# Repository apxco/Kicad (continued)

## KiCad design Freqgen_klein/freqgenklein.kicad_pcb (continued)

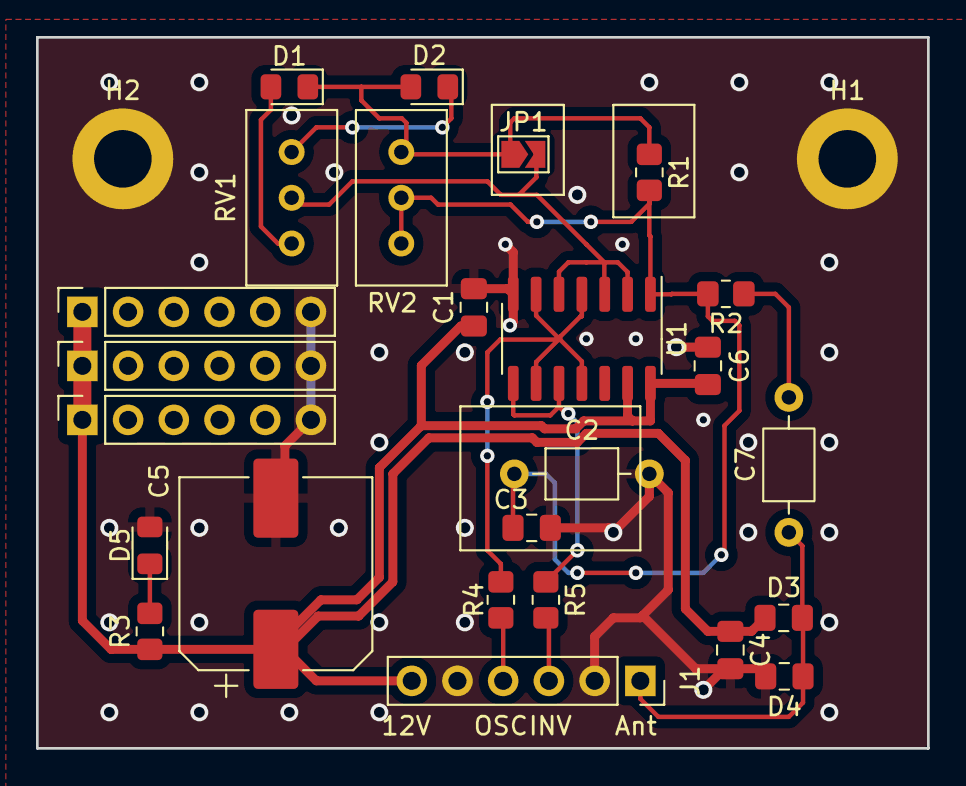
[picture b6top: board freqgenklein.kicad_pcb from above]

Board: 2 copper layers, 49.5 x 39.5 mm, 27 parts (0 on the bottom side), 14 nets.

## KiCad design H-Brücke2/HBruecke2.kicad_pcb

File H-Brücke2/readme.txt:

Aufbau einer H-Brücke mit eigenem Oszillator.

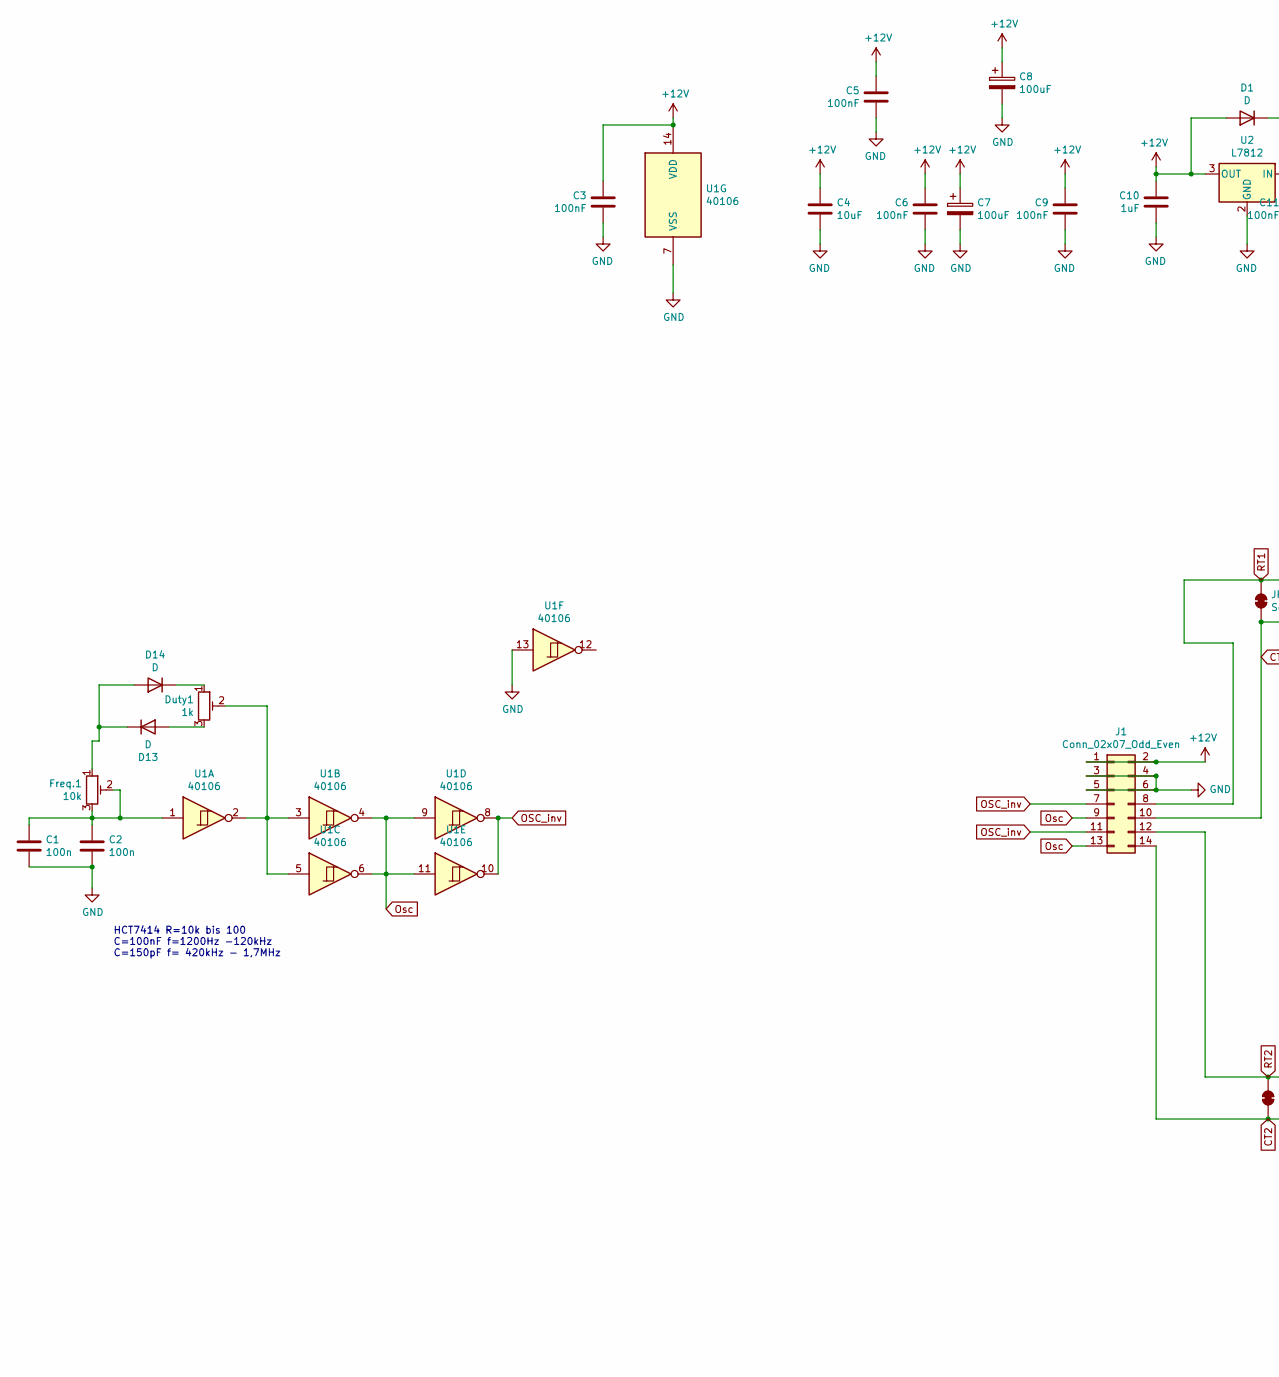
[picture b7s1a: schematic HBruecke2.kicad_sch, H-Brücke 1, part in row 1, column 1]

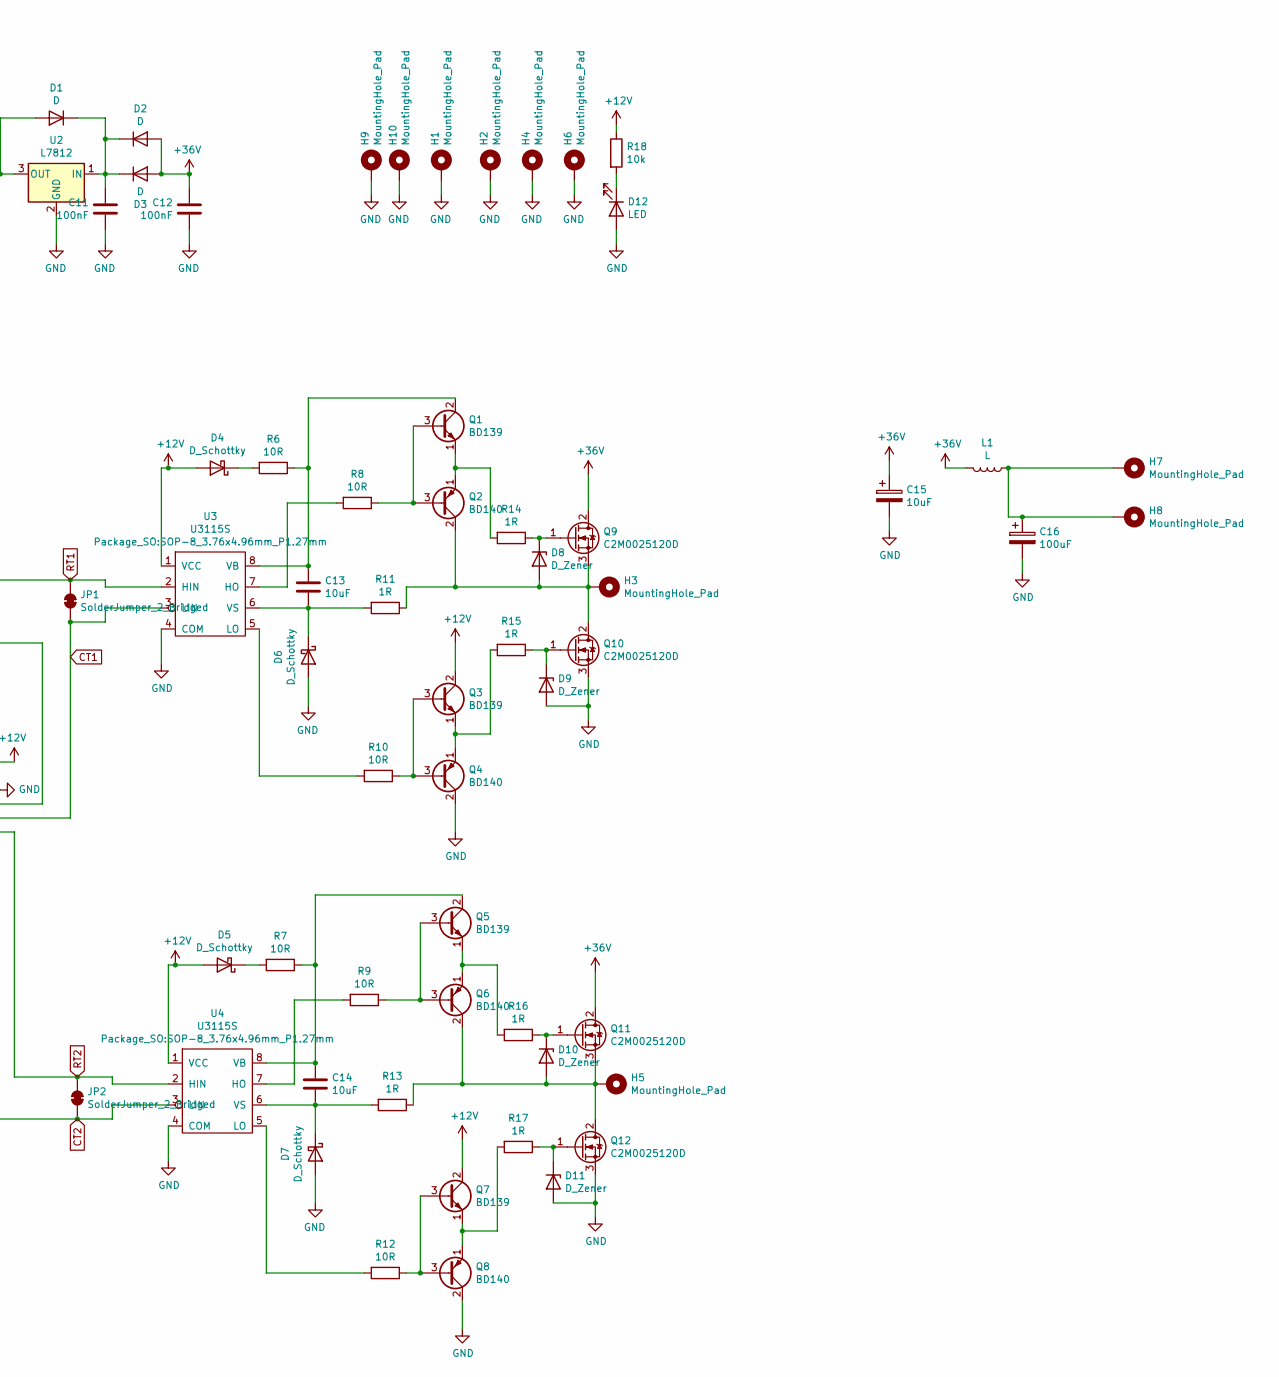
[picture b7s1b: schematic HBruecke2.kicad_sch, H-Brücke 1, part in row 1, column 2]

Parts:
C1: 100n; C_Axial_L3.8mm_D2.6mm_P7.50mm_Horizontal
C2: 100n; C_0805_2012Metric_Pad1.18x1.45mm_HandSolder
C3, C5, C6: 100nF; C_0805_2012Metric_Pad1.18x1.45mm_HandSolder
C4, C14: 10uF; C_1210_3225Metric_Pad1.33x2.70mm_HandSolder
C7, C8: 100uF; CP_Elec_10x10.5
C9, C11, C12: 100nF; C_0805_2012Metric_Pad1.15x1.40mm_HandSolder
C10: 1uF; C_0805_2012Metric_Pad1.15x1.40mm_HandSolder
C13: 10uF; C_1210_3225Metric_Pad1.42x2.65mm_HandSolder
C15: 10uF; C_Rect_L28.0mm_W10.0mm_P22.50mm_MKS4
C16: 100uF; CP_Radial_D22.0mm_P10.00mm_SnapIn
D1, D13, D14: D; D_0805_2012Metric_Pad1.15x1.40mm_HandSolder
D2: D; D_A-405_P7.62mm_Horizontal
D3: D; D_SOD-123
D4, D5, D6, D7: D_Schottky; D_SOD-123
D8, D9, D10, D11: D_Zener; D_SOD-123
D12: LED; LED_0805_2012Metric_Pad1.15x1.40mm_HandSolder
Duty1: 1k; Potentiometer_Bourns_3296W_Vertical
Freq.1: 10k; Potentiometer_Bourns_3296W_Vertical
H1, H2: MountingHole_Pad; MountingHole_3.2mm_M3_DIN965_Pad
H3, H4, H5, H6, H7, H8: MountingHole_Pad; MountingHole_2.5mm_Pad_Via
H9, H10: MountingHole_Pad; TestPoint_THTPad_D2.5mm_Drill1.2mm
J1: Conn_02x07_Odd_Even; PinHeader_2x07_P2.54mm_Vertical
JP1, JP2: SolderJumper_2_Bridged; SolderJumper-2_P1.3mm_Open_RoundedPad1.0x1.5mm
L1: L; L_Toroid_Vertical_L16.3mm_W7.1mm_P7.11mm_Pulse_H
Q1, Q3, Q5, Q7: BD139; TO-126-3_Vertical
Q2, Q4, Q6, Q8: BD140; TO-126-3_Vertical
Q9, Q10, Q11, Q12: C2M0025120D; TO-247-3_Vertical
R6, R7, R8, R9, R10, R12: 10R; R_0805_2012Metric_Pad1.20x1.40mm_HandSolder
R11, R13, R14, R15, R16, R17: 1R; R_1206_3216Metric_Pad1.30x1.75mm_HandSolder
R18: 10k; R_0805_2012Metric_Pad1.20x1.40mm_HandSolder
U1: 40106; SO-14_3.9x8.65mm_P1.27mm
U2: L7812; TO-252-2
U3, U4: U3115S; SOP-8_3.76x4.96mm_P1.27mm

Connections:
+12V: C3.1, C4.1, C5.1, C6.1, C7.1, C8.1, C9.1, C10.1, D1.2 (A), D4.2 (A), D5.2 (A), J1.1, J1.2, Q3.2 (C), Q7.2 (C), R18.1, U1.14 (VDD), U2.3 (OUT), U3.1 (VCC), U4.1 (VCC)
+36V: C12.1, C15.1, D2.2 (A), D3.2 (A), L1.2, Q9.2 (D), Q11.2 (D)
CT1: J1.10, JP1.2 (B), U3.3 (LIN)
CT2: J1.14, JP2.2 (B), U4.3 (LIN)
GND: C1.2, C2.2, C3.2, C4.2, C5.2, C6.2, C7.2, C8.2, C9.2, C10.2, C11.2, C12.2, C15.2, C16.2, D6.2 (A), D7.2 (A), D9.2 (A), D11.2 (A), D12.2 (A), H1.1, H2.1, H4.1, H6.1, H9.1, H10.1, J1.3, J1.4, J1.5, J1.6, Q4.2 (C), Q8.2 (C), Q10.3 (S), Q12.3 (S), U1.7 (VSS), U1.13, U2.2 (GND), U3.4 (COM), U4.4 (COM)
unnamed: C1.1, C2.1, Freq.1.2, Freq.1.3, U1.1
unnamed: C11.1, D1.1 (K), D2.1 (K), D3.1 (K), U2.1 (IN)
unnamed: C13.1, Q1.2 (C), R6.1, U3.8 (VB)
unnamed: C13.2, D6.1 (K), R11.2, U3.6 (VS)
unnamed: C14.1, Q5.2 (C), R7.1, U4.8 (VB)
unnamed: C14.2, D7.1 (K), R13.2, U4.6 (VS)
unnamed: C16.1, H7.1, H8.1, L1.1
unnamed: D4.1 (K), R6.2
unnamed: D5.1 (K), R7.2
unnamed: D8.1 (K), Q9.1 (G), R14.1
unnamed: D8.2 (A), H3.1, Q2.2 (C), Q9.3 (S), Q10.2 (D), R11.1
unnamed: D9.1 (K), Q10.1 (G), R15.1
unnamed: D10.1 (K), Q11.1 (G), R16.1
unnamed: D10.2 (A), H5.1, Q6.2 (C), Q11.3 (S), Q12.2 (D), R13.1
unnamed: D11.1 (K), Q12.1 (G), R17.1
unnamed: D12.1 (K), R18.2
unnamed: D13.1 (K), D14.2 (A), Freq.1.1
unnamed: D13.2 (A), Duty1.3
unnamed: D14.1 (K), Duty1.1
unnamed: Duty1.2, U1.2, U1.3, U1.5
unnamed: Q1.1 (E), Q2.1 (E), R14.2
unnamed: Q1.3 (B), Q2.3 (B), R8.1
unnamed: Q3.1 (E), Q4.1 (E), R15.2
unnamed: Q3.3 (B), Q4.3 (B), R10.1
unnamed: Q5.1 (E), Q6.1 (E), R16.2
unnamed: Q5.3 (B), Q6.3 (B), R9.1
unnamed: Q7.1 (E), Q8.1 (E), R17.2
unnamed: Q7.3 (B), Q8.3 (B), R12.1
unnamed: R8.2, U3.7 (HO)
unnamed: R9.2, U4.7 (HO)
unnamed: R10.2, U3.5 (LO)
unnamed: R12.2, U4.5 (LO)
OSC_inv: J1.7, J1.11, U1.8, U1.10
Osc: J1.9, J1.13, U1.4, U1.6, U1.9, U1.11
RT1: J1.8, JP1.1 (A), U3.2 (HIN)
RT2: J1.12, JP2.1 (A), U4.2 (HIN)

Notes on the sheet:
HCT7414 R=10k bis 100 C=100nF f=1200Hz -120kHz C=150pF f= 420kHz - 1,7MHz

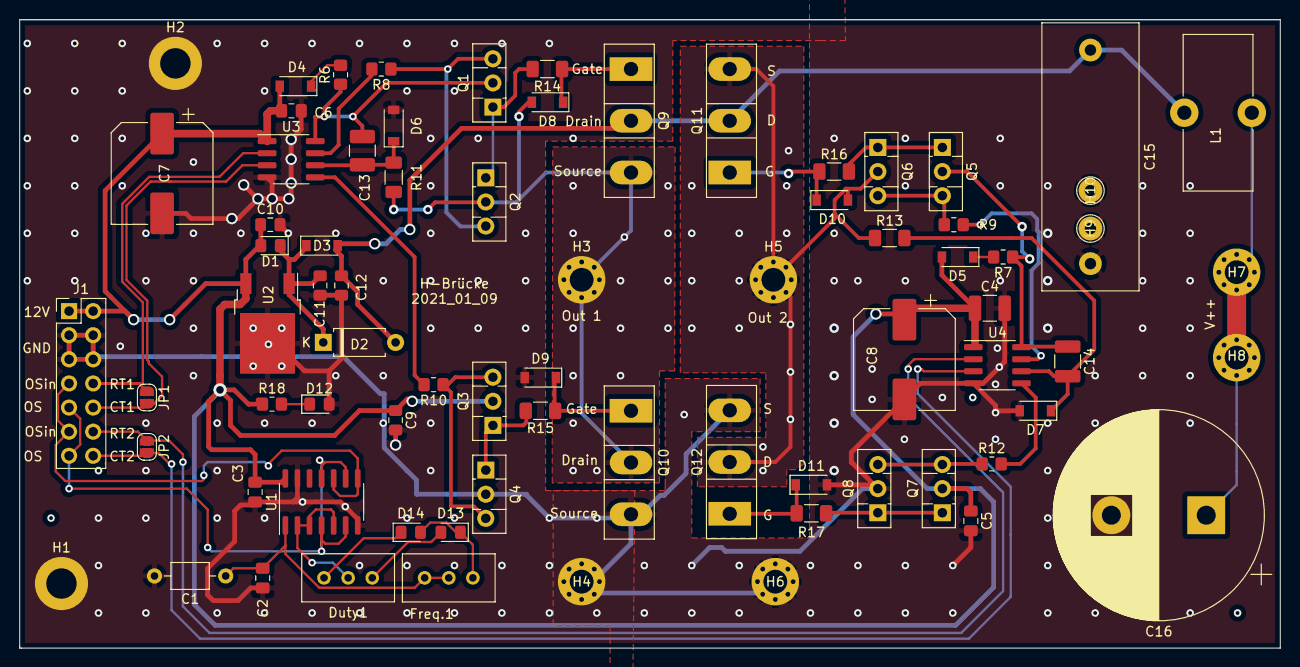
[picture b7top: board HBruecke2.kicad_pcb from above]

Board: 2 copper layers, 132.8 x 66.2 mm, 75 parts (0 on the bottom side), 41 nets.
